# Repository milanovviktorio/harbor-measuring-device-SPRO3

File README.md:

# harbor-measuring-device-SPRO3
SPRO3, SDU Electronics

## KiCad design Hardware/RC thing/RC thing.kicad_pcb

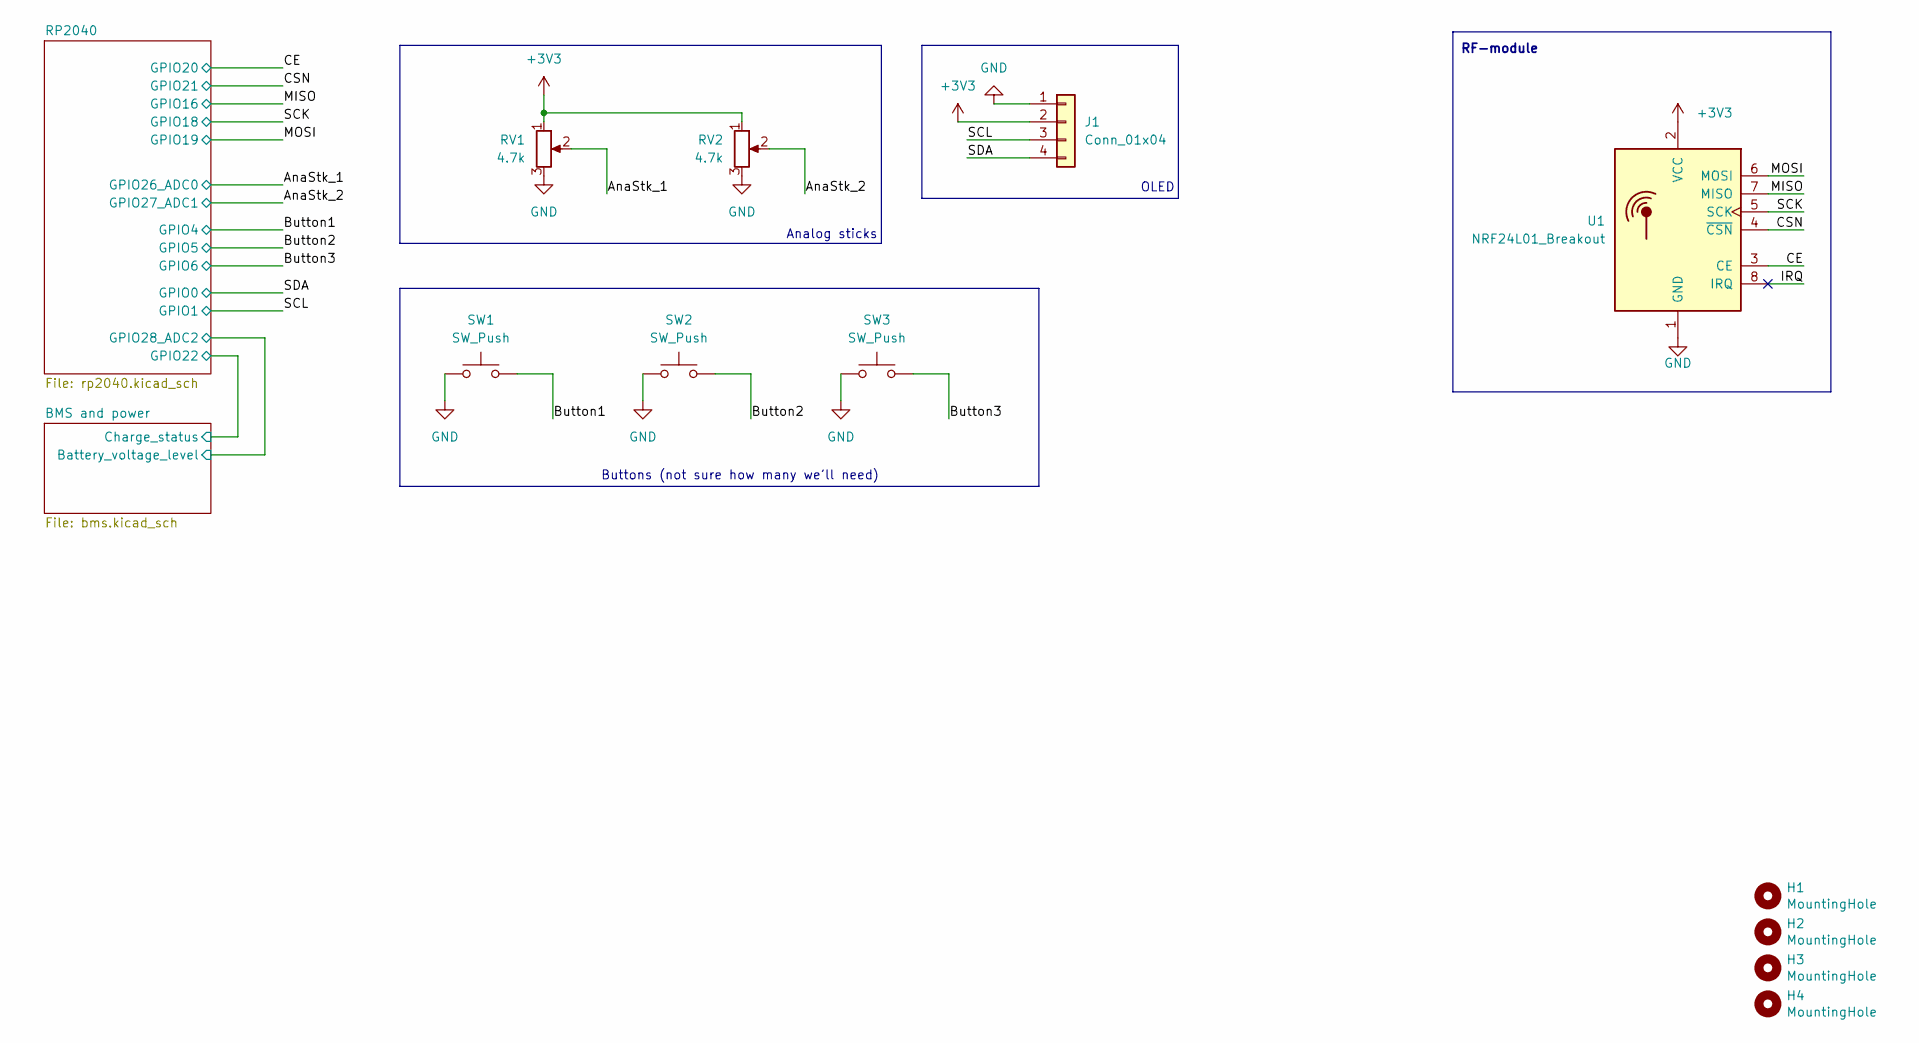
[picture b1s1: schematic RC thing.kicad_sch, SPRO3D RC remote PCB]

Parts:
H1, H2, H3, H4: MountingHole; MountingHole_2.7mm_M2.5
J1: Conn_01x04; JST_PH_B4B-PH-K_1x04_P2.00mm_Vertical
RV1, RV2: 4.7k; JST_PH_B3B-PH-K_1x03_P2.00mm_Vertical
SW1, SW2, SW3: SW_Push; JST_PH_B2B-PH-K_1x02_P2.00mm_Vertical
U1: NRF24L01_Breakout; PinHeader_2x04_P2.54mm_Vertical

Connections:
+3V3: J1.2, RV1.1, RV2.1, U1.2 (VCC); also elsewhere on the board
/AnaStk_1: RV1.2; also elsewhere on the board
/AnaStk_2: RV2.2; also elsewhere on the board
/Button1: SW1.2; also elsewhere on the board
/Button2: SW2.2; also elsewhere on the board
/Button3: SW3.2; also elsewhere on the board
/CE: U1.3 (CE); also elsewhere on the board
/CSN: U1.4 (~CSN); also elsewhere on the board
/IRQ: U1.8 (IRQ)
/MISO: U1.7 (MISO); also elsewhere on the board
/MOSI: U1.6 (MOSI); also elsewhere on the board
/SCK: U1.5 (SCK); also elsewhere on the board
/SCL: J1.3; also elsewhere on the board
/SDA: J1.4; also elsewhere on the board
GND: J1.1, RV1.3, RV2.3, SW1.1, SW2.1, SW3.1, U1.1 (GND); also elsewhere on the board

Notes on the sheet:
Buttons (not sure how many we'll need)
RF-module
OLED
Analog sticks

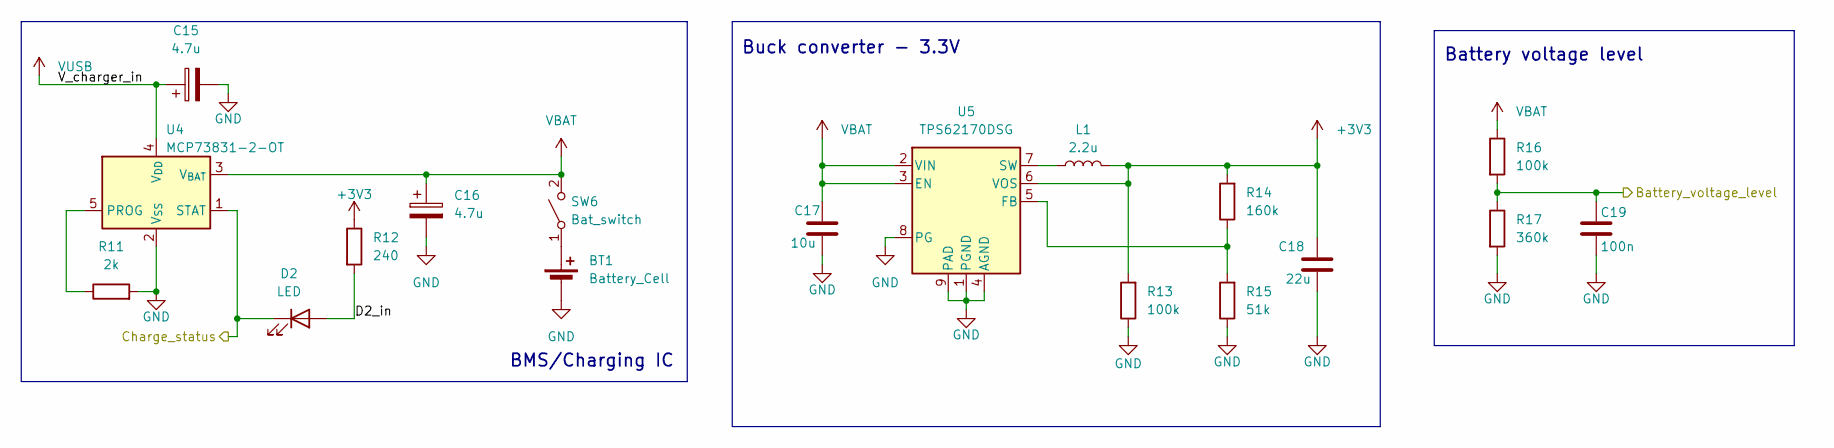
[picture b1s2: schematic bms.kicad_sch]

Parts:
BT1: Battery_Cell; JST_PH_B2B-PH-K_1x02_P2.00mm_Vertical
C15, C16: 4.7u; C_0805_2012Metric_Pad1.18x1.45mm_HandSolder
C17: 10u; C_0805_2012Metric_Pad1.18x1.45mm_HandSolder
C18: 22u; C_0805_2012Metric_Pad1.18x1.45mm_HandSolder
C19: 100n; C_0603_1608Metric_Pad1.08x0.95mm_HandSolder
D2: LED; D_0603_1608Metric_Pad1.05x0.95mm_HandSolder
L1: 2.2u; L_APV_ANR252012
R11: 2k; R_0603_1608Metric_Pad0.98x0.95mm_HandSolder
R12: 240; R_0603_1608Metric_Pad0.98x0.95mm_HandSolder
R13, R16: 100k; R_0603_1608Metric_Pad0.98x0.95mm_HandSolder
R14: 160k; R_0603_1608Metric_Pad0.98x0.95mm_HandSolder
R15: 51k; R_0603_1608Metric_Pad0.98x0.95mm_HandSolder
R17: 360k; R_0603_1608Metric_Pad0.98x0.95mm_HandSolder
SW6: Bat_switch; JST_PH_B2B-PH-K_1x02_P2.00mm_Vertical
U4: MCP73831-2-OT; SOT-23-5
U5: TPS62170DSG; WSON-8-1EP_2x2mm_P0.5mm_EP0.9x1.6mm_ThermalVias

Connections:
+3V3: C18.1, L1.2, R12.1, R13.2, R14.2, U5.6 (VOS); also elsewhere on the board
/BMS and power/D2_in: D2.2 (A), R12.2
/RP2040/GPIO22: D2.1 (K), U4.1 (STAT); also elsewhere on the board
/RP2040/GPIO28_ADC2: C19.1, R16.2, R17.1; also elsewhere on the board
GND: BT1.2 (-), C15.2, C16.2, C17.2, C18.2, C19.2, R11.2, R13.1, R15.1, R17.2, U4.2 (V_{SS}), U5.1 (PGND), U5.4 (AGND), U5.8 (PG), U5.9 (PAD); also elsewhere on the board
unnamed: BT1.1 (+), SW6.1 (A)
unnamed: R11.1, U4.5 (PROG)
unnamed: R14.1, R15.2, U5.5 (FB)
unnamed: L1.1, U5.7 (SW)
VBAT: C16.1, C17.1, R16.1, SW6.2 (B), U4.3 (V_{BAT}), U5.2 (VIN), U5.3 (EN)
VUSB: C15.1, U4.4 (V_{DD}); also elsewhere on the board

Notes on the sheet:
BMS/Charging IC
Battery voltage level
Buck converter - 3.3V

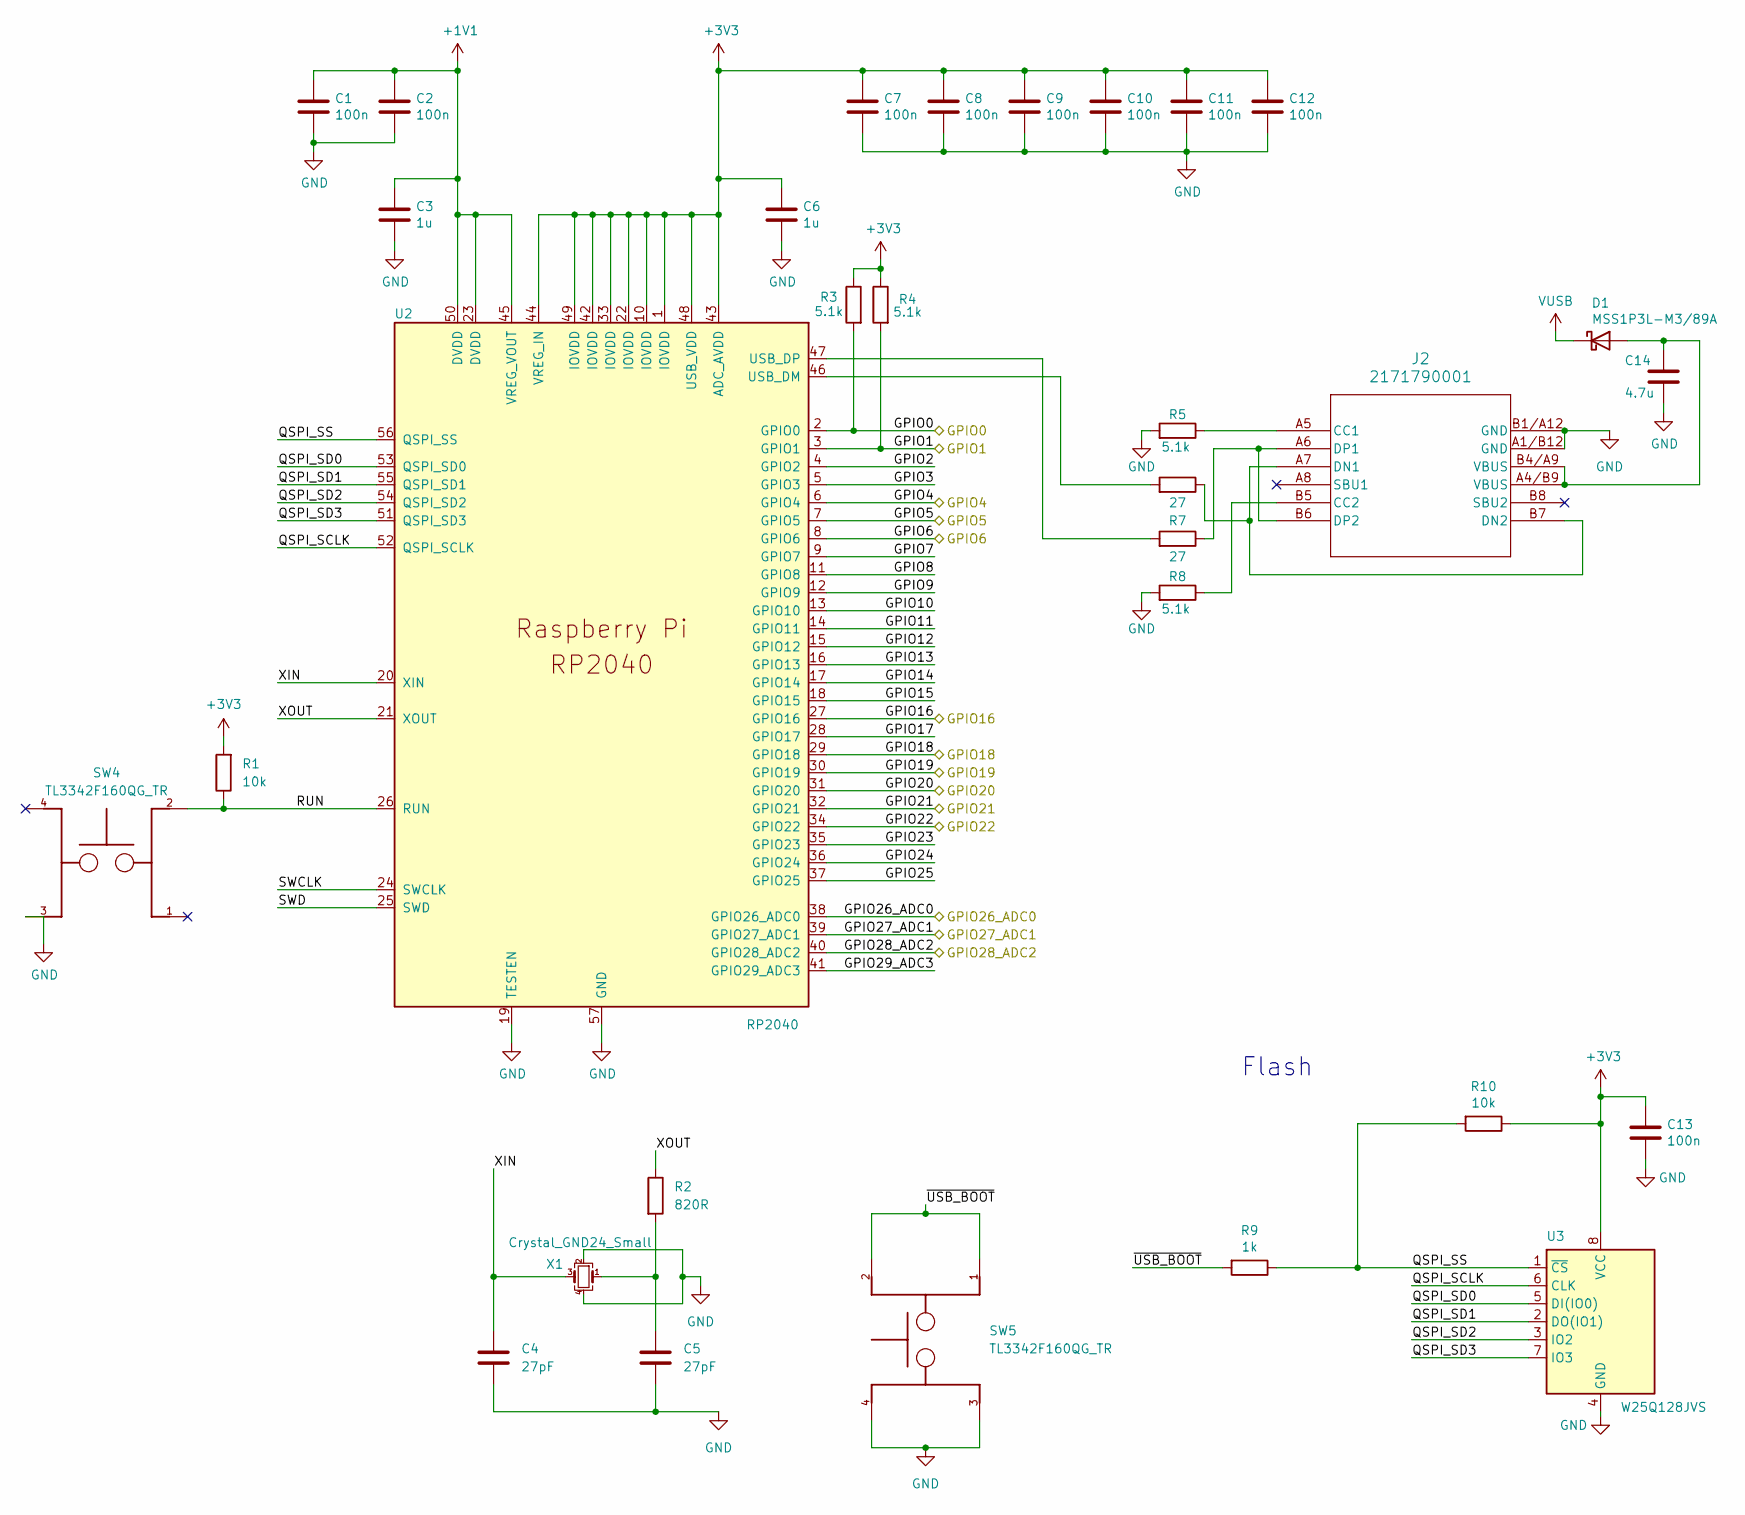
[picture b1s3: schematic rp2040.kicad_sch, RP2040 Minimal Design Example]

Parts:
C1, C2, C7, C8, C9, C10, C11, C12, C13: 100n; C_0603_1608Metric_Pad1.08x0.95mm_HandSolder
C3, C6: 1u; C_0603_1608Metric_Pad1.08x0.95mm_HandSolder
C4, C5: 27pF; C_0603_1608Metric_Pad1.08x0.95mm_HandSolder
C14: 4.7u; C_0603_1608Metric_Pad1.08x0.95mm_HandSolder
D1: MSS1P3L-M3/89A; Vishay_SMPA
J2: 2171790001; 2171790001_MOL
R1: 10k; C_0603_1608Metric_Pad1.08x0.95mm_HandSolder
R2: 820R; R_0603_1608Metric_Pad0.98x0.95mm_HandSolder
R3, R4, R5, R8: 5.1k; R_0603_1608Metric_Pad0.98x0.95mm_HandSolder
R6, R7: 27; R_0603_1608Metric_Pad0.98x0.95mm_HandSolder
R9: 1k; R_0603_1608Metric_Pad0.98x0.95mm_HandSolder
R10: 10k; R_0603_1608Metric_Pad0.98x0.95mm_HandSolder
SW4, SW5: TL3342F160QG_TR; SW_TL3342F160QG_TR
U2: RP2040; QFN-56-1EP_7x7mm_P0.4mm_EP3.2x3.2mm
U3: W25Q128JVS; SOIC-8_5.3x5.3mm_P1.27mm
X1: Crystal_GND24_Small; Crystal_SMD_Abracon_ABM8G-4Pin_3.2x2.5mm

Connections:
+1V1: C1.1, C2.1, C3.1, U2.23 (DVDD), U2.45 (VREG_VOUT), U2.50 (DVDD)
+3V3: C6.1, C7.1, C8.1, C9.1, C10.1, C11.1, C12.1, C13.1, R1.2, R3.1, R4.1, R10.1, U2.1 (IOVDD), U2.10 (IOVDD), U2.22 (IOVDD), U2.33 (IOVDD), U2.42 (IOVDD), U2.43 (ADC_AVDD), U2.44 (VREG_IN), U2.48 (USB_VDD), U2.49 (IOVDD), U3.8 (VCC); also elsewhere on the board
/AnaStk_1: U2.38 (GPIO26_ADC0); also elsewhere on the board
/AnaStk_2: U2.39 (GPIO27_ADC1); also elsewhere on the board
/Button1: U2.6 (GPIO4); also elsewhere on the board
/Button2: U2.7 (GPIO5); also elsewhere on the board
/Button3: U2.8 (GPIO6); also elsewhere on the board
/CE: U2.31 (GPIO20); also elsewhere on the board
/CSN: U2.32 (GPIO21); also elsewhere on the board
/MISO: U2.27 (GPIO16); also elsewhere on the board
/MOSI: U2.30 (GPIO19); also elsewhere on the board
/RP2040/GPIO2: U2.4 (GPIO2)
/RP2040/GPIO3: U2.5 (GPIO3)
/RP2040/GPIO7: U2.9 (GPIO7)
/RP2040/GPIO8: U2.11 (GPIO8)
/RP2040/GPIO9: U2.12 (GPIO9)
/RP2040/GPIO10: U2.13 (GPIO10)
/RP2040/GPIO11: U2.14 (GPIO11)
/RP2040/GPIO12: U2.15 (GPIO12)
/RP2040/GPIO13: U2.16 (GPIO13)
/RP2040/GPIO14: U2.17 (GPIO14)
/RP2040/GPIO15: U2.18 (GPIO15)
/RP2040/GPIO17: U2.28 (GPIO17)
/RP2040/GPIO22: U2.34 (GPIO22); also elsewhere on the board
/RP2040/GPIO23: U2.35 (GPIO23)
/RP2040/GPIO24: U2.36 (GPIO24)
/RP2040/GPIO25: U2.37 (GPIO25)
/RP2040/GPIO28_ADC2: U2.40 (GPIO28_ADC2); also elsewhere on the board
/RP2040/GPIO29_ADC3: U2.41 (GPIO29_ADC3)
/RP2040/QSPI_SCLK: U2.52 (QSPI_SCLK), U3.6 (CLK)
/RP2040/QSPI_SD0: U2.53 (QSPI_SD0), U3.5 (DI(IO0))
/RP2040/QSPI_SD1: U2.55 (QSPI_SD1), U3.2 (DO(IO1))
/RP2040/QSPI_SD2: U2.54 (QSPI_SD2), U3.3 (IO2)
/RP2040/QSPI_SD3: U2.51 (QSPI_SD3), U3.7 (IO3)
/RP2040/QSPI_SS: R9.1, R10.2, U2.56 (QSPI_SS), U3.1 (~CS)
/RP2040/RUN: R1.1, SW4.2, U2.26 (RUN)
/RP2040/SWCLK: U2.24 (SWCLK)
/RP2040/SWD: U2.25 (SWD)
/RP2040/XIN: C4.1, U2.20 (XIN), X1.3
/RP2040/XOUT: R2.1, U2.21 (XOUT)
/RP2040/~USB_BOOT: R9.2, SW5.1, SW5.2
/SCK: U2.29 (GPIO18); also elsewhere on the board
/SCL: R4.2, U2.3 (GPIO1); also elsewhere on the board
/SDA: R3.2, U2.2 (GPIO0); also elsewhere on the board
GND: C1.2, C2.2, C3.2, C4.2, C5.2, C6.2, C7.2, C8.2, C9.2, C10.2, C11.2, C12.2, C13.2, C14.2, J2.A1/B12 (GND), J2.B1/A12 (GND), R5.2, R8.2, SW4.3, SW5.3, SW5.4, U2.19 (TESTEN), U2.57 (GND), U3.4 (GND), X1.2, X1.4; also elsewhere on the board
unnamed: C5.1, R2.2, X1.1
unnamed: C14.1, D1.2 (A), J2.A4/B9 (VBUS), J2.B4/A9 (VBUS)
unnamed: J2.A5 (CC1), R5.1
unnamed: J2.B5 (CC2), R8.1
unnamed: J2.A7 (DN1), J2.B7 (DN2), R6.1
unnamed: J2.A6 (DP1), J2.B6 (DP2), R7.1
unnamed: R6.2, U2.46 (USB_DM)
unnamed: R7.2, U2.47 (USB_DP)
VUSB: D1.1 (K); also elsewhere on the board

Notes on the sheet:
Flash

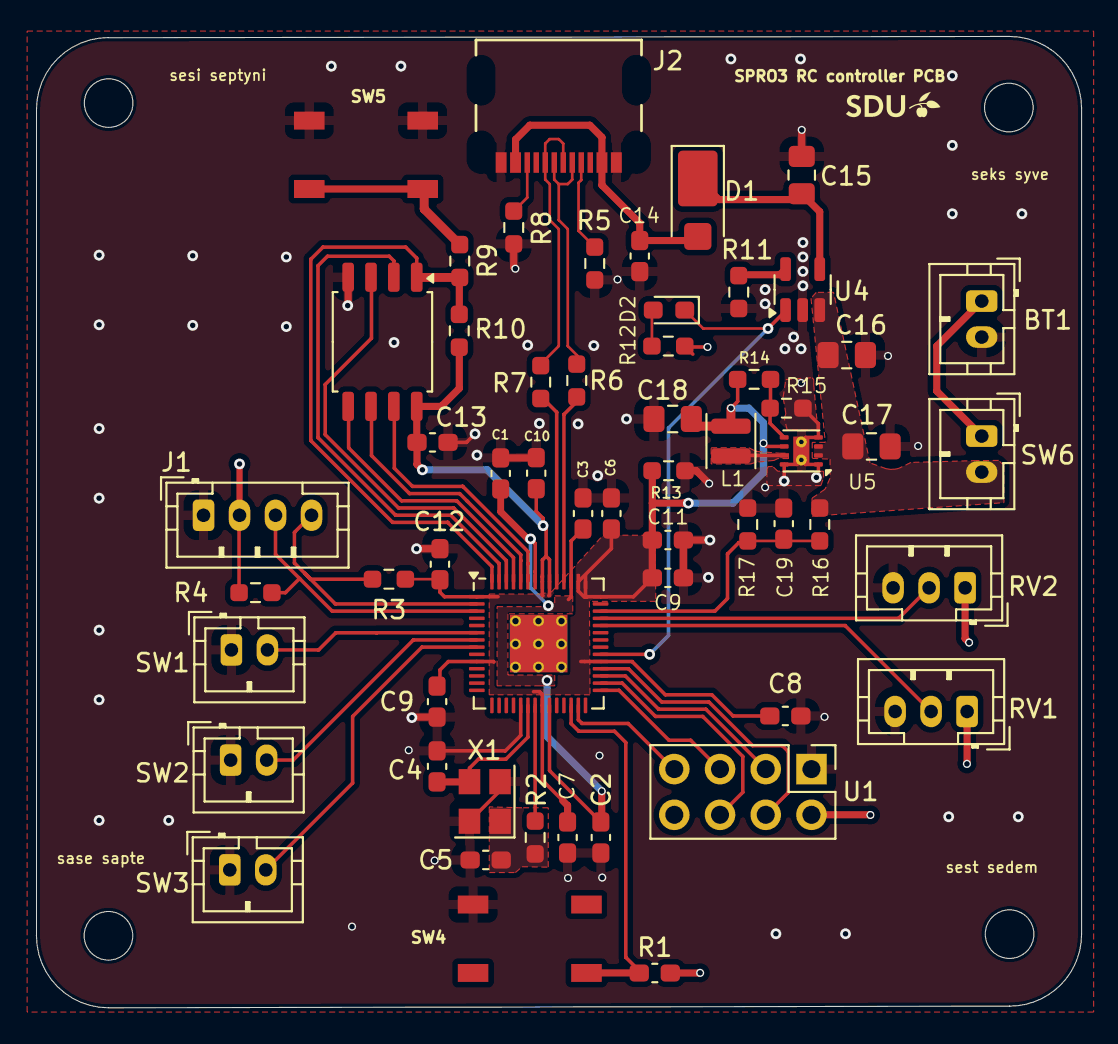
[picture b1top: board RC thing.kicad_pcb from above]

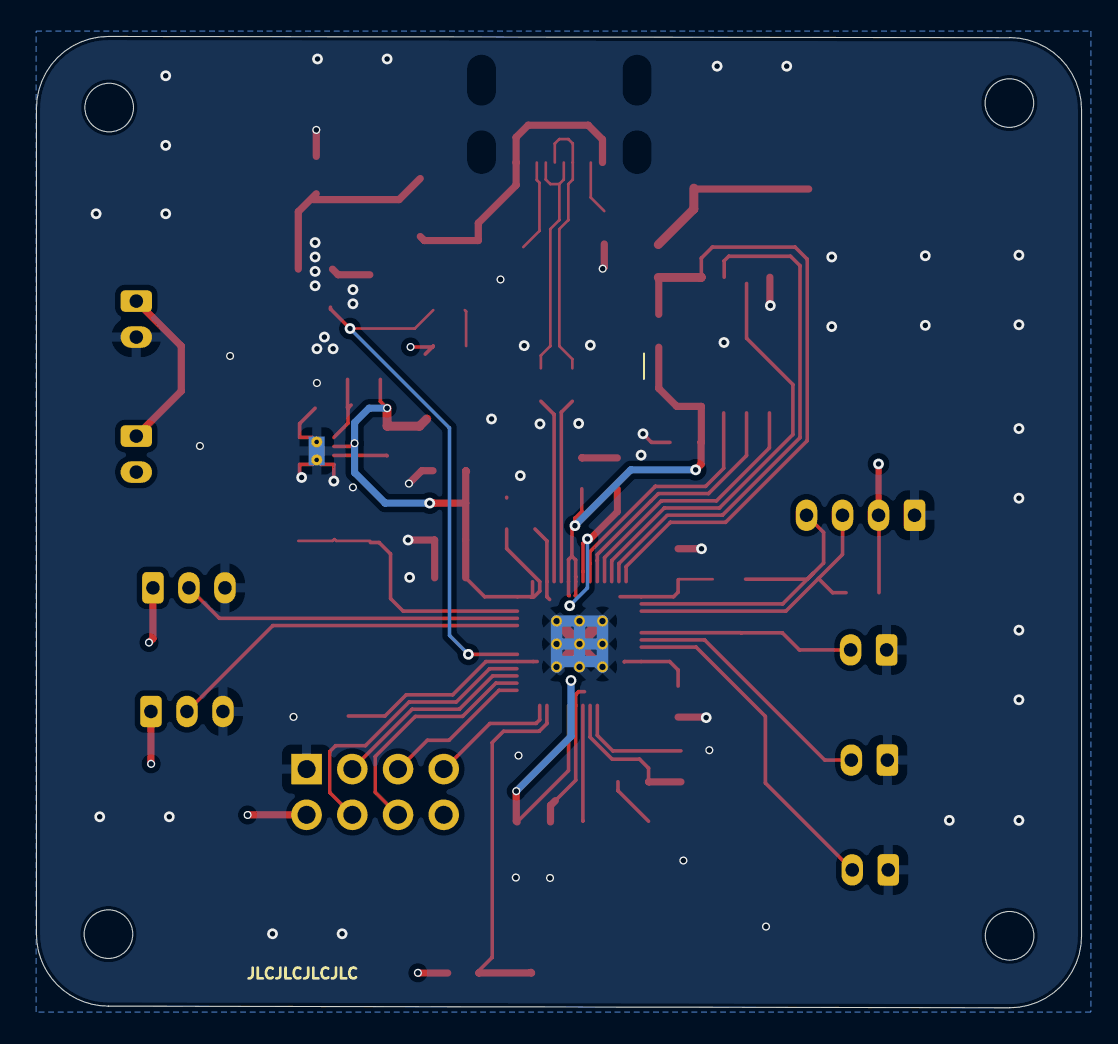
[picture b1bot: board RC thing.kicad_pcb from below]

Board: 4 copper layers, 58.1 x 54.0 mm, 61 parts (4 on the bottom side), 42 nets.

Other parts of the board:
C9#2: 100nx2; C_0603_1608Metric_Pad1.08x0.95mm_HandSolder

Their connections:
+3V3: C9#2.1; also elsewhere on the board
GND: C9#2.2; also elsewhere on the board

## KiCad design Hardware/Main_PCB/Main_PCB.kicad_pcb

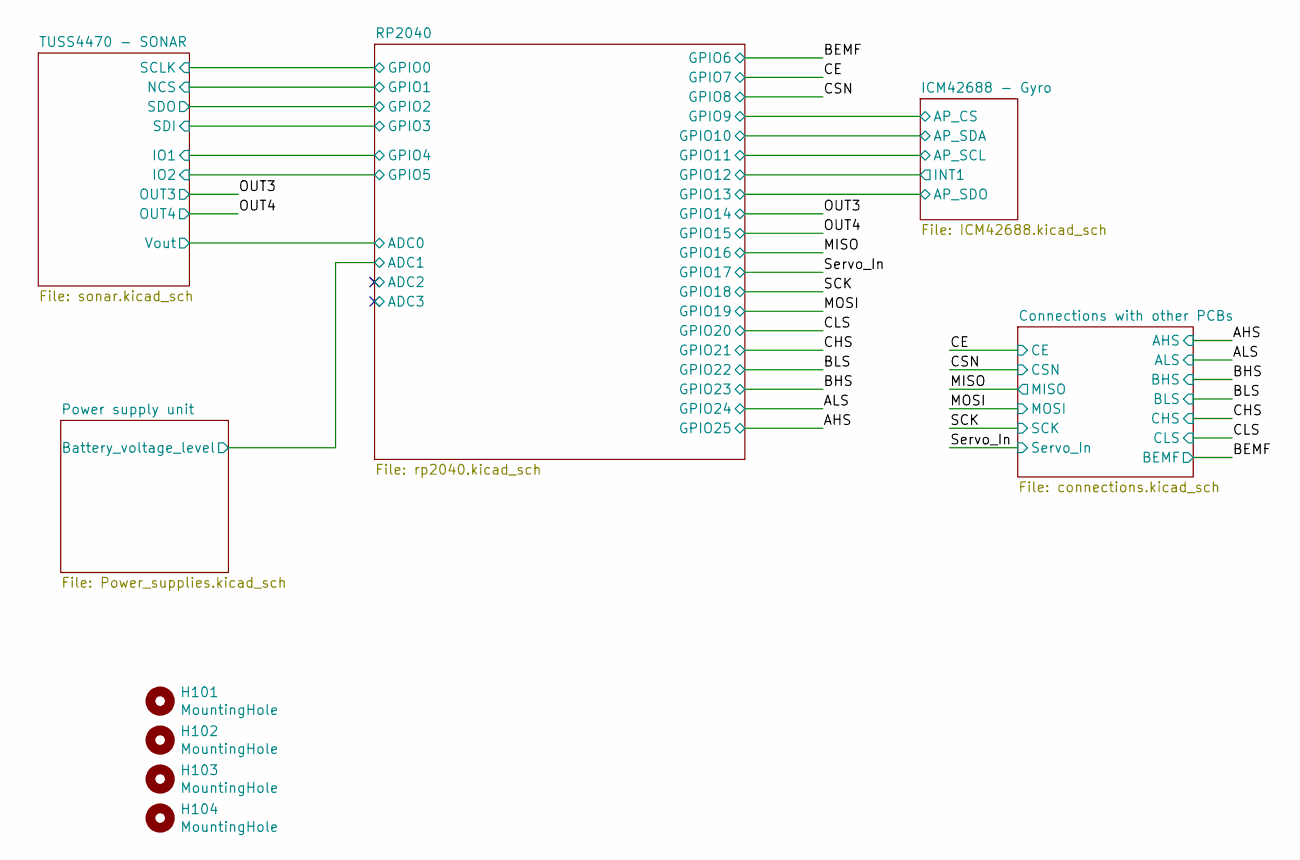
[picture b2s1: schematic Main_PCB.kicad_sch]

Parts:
H101, H102, H103, H104: MountingHole; MountingHole_2.7mm_M2.5

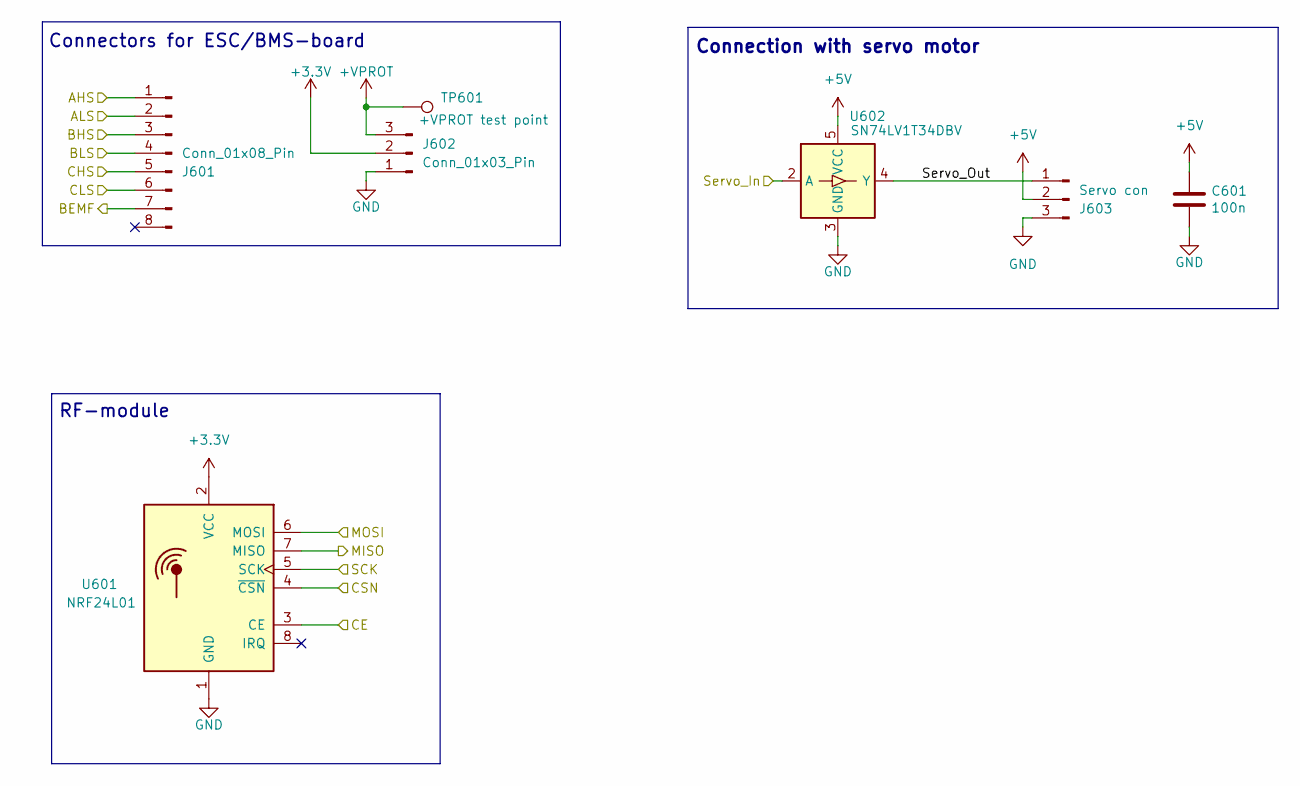
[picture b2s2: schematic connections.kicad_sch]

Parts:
C601: 100n; C_0603_1608Metric_Pad1.08x0.95mm_HandSolder
J601: Conn_01x08_Pin; JST_PH_B8B-PH-K_1x08_P2.00mm_Vertical
J602: Conn_01x03_Pin; JST_PH_B3B-PH-K_1x03_P2.00mm_Vertical
J603: Servo con; JST_PH_B3B-PH-K_1x03_P2.00mm_Vertical
TP601: +VPROT test point; TestPoint_Pad_D1.0mm
U601: NRF24L01; PinSocket_2x04_P2.54mm_Vertical
U602: SN74LV1T34DBV; SOT-23-5

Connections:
+3.3V: J602.2, U601.2 (VCC); also elsewhere on the board
+5V: C601.1, J603.2, U602.5 (VCC); also elsewhere on the board
+VPROT: J602.3, TP601.1; also elsewhere on the board
/AHS: J601.1; also elsewhere on the board
/ALS: J601.2; also elsewhere on the board
/BEMF: J601.7; also elsewhere on the board
/BHS: J601.3; also elsewhere on the board
/BLS: J601.4; also elsewhere on the board
/CE: U601.3 (CE); also elsewhere on the board
/CHS: J601.5; also elsewhere on the board
/CLS: J601.6; also elsewhere on the board
/CSN: U601.4 (~CSN); also elsewhere on the board
/Connections with other PCBs/Servo_Out: J603.1, U602.4 (Y)
/MISO: U601.7 (MISO); also elsewhere on the board
/MOSI: U601.6 (MOSI); also elsewhere on the board
/SCK: U601.5 (SCK); also elsewhere on the board
/Servo_In: U602.2 (A); also elsewhere on the board
GND: C601.2, J602.1, J603.3, U601.1 (GND), U602.3 (GND); also elsewhere on the board

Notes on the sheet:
Connection with servo motor
RF-module
Connectors for ESC/BMS-board

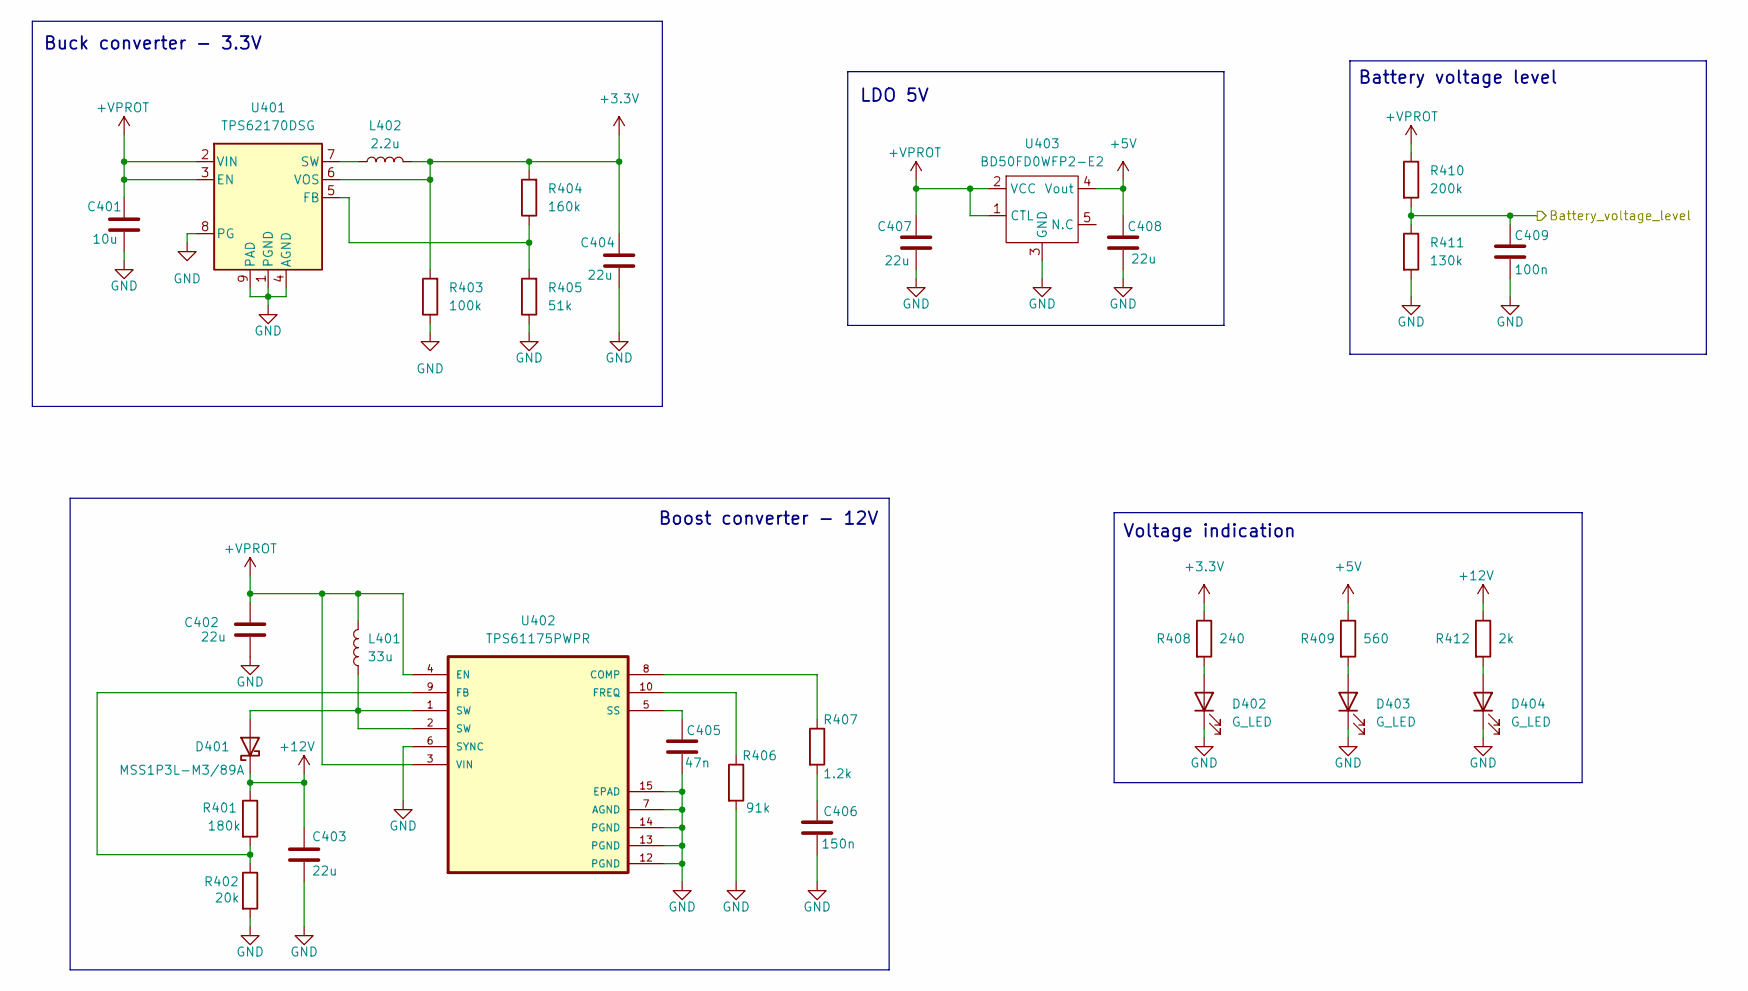
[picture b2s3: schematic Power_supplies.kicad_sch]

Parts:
C401: 10u; C_0805_2012Metric_Pad1.18x1.45mm_HandSolder
C402, C403, C404, C407, C408: 22u; C_0805_2012Metric_Pad1.18x1.45mm_HandSolder
C405: 47n; C_0805_2012Metric_Pad1.18x1.45mm_HandSolder
C406: 150n; C_0805_2012Metric_Pad1.18x1.45mm_HandSolder
C409: 100n; C_0603_1608Metric_Pad1.08x0.95mm_HandSolder
D401: MSS1P3L-M3/89A; Vishay_SMPA
D402, D403, D404: G_LED; D_0603_1608Metric_Pad1.05x0.95mm_HandSolder
L401: 33u; VLCF4018
L402: 2.2u; L_APV_ANR252012
R401: 180k; R_0603_1608Metric_Pad0.98x0.95mm_HandSolder
R402: 20k; R_0603_1608Metric_Pad0.98x0.95mm_HandSolder
R403: 100k; R_0603_1608Metric_Pad0.98x0.95mm_HandSolder
R404: 160k; R_0603_1608Metric_Pad0.98x0.95mm_HandSolder
R405: 51k; R_0603_1608Metric_Pad0.98x0.95mm_HandSolder
R406: 91k; R_0603_1608Metric_Pad0.98x0.95mm_HandSolder
R407: 1.2k; R_0603_1608Metric_Pad0.98x0.95mm_HandSolder
R408: 240; R_0603_1608Metric_Pad0.98x0.95mm_HandSolder
R409: 560; R_0603_1608Metric_Pad0.98x0.95mm_HandSolder
R410: 200k; R_0603_1608Metric_Pad0.98x0.95mm_HandSolder
R411: 130k; R_0603_1608Metric_Pad0.98x0.95mm_HandSolder
R412: 2k; R_0603_1608Metric_Pad0.98x0.95mm_HandSolder
U401: TPS62170DSG; WSON-8-1EP_2x2mm_P0.5mm_EP0.9x1.6mm_ThermalVias
U402: TPS61175PWPR; IC_TPS27S100BPWPR
U403: BD50FD0WFP2-E2; TO-263-5_TabPin3

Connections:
+3.3V: C404.1, L402.2, R403.2, R404.2, R408.1, U401.6 (VOS); also elsewhere on the board
+5V: C408.1, R409.1, U403.4 (Vout); also elsewhere on the board
+12V: C403.1, D401.1 (K), R401.1, R412.1; also elsewhere on the board
+VPROT: C401.1, C402.2, C407.1, L401.2, R410.1, U401.2 (VIN), U401.3 (EN), U402.3 (VIN), U402.4 (EN), U403.1 (CTL), U403.2 (VCC); also elsewhere on the board
/Power supply unit/Battery_voltage_level: C409.1, R410.2, R411.1; also elsewhere on the board
GND: C401.2, C402.1, C403.2, C404.2, C405.2, C406.2, C407.2, C408.2, C409.2, D402.1 (K), D403.1 (K), D404.1 (K), R402.2, R403.1, R405.1, R406.2, R411.2, U401.1 (PGND), U401.4 (AGND), U401.8 (PG), U401.9 (PAD), U402.6 (SYNC), U402.7 (AGND), U402.12 (PGND), U402.13 (PGND), U402.14 (PGND), U402.15 (EPAD), U403.3 (GND); also elsewhere on the board
unnamed: C406.1, R407.2
unnamed: D401.2 (A), L401.1, U402.1 (SW), U402.2 (SW)
unnamed: D402.2 (A), R408.2
unnamed: D403.2 (A), R409.2
unnamed: D404.2 (A), R412.2
unnamed: R404.1, R405.2, U401.5 (FB)
unnamed: L402.1, U401.7 (SW)
unnamed: R407.1, U402.8 (COMP)
unnamed: R401.2, R402.1, U402.9 (FB)
unnamed: R406.1, U402.10 (FREQ)
unnamed: C405.1, U402.5 (SS)

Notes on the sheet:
Boost converter - 12V
LDO 5V
Buck converter - 3.3V
Voltage indication
Battery voltage level
